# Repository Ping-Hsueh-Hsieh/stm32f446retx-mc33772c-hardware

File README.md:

# TODO

- [x] fill region: In1.Cu with GND
- [x] change 16MHz crystal to 8MHz, since 8MHz is cheaper and more available.
- [x] USB OTG FS: VBUS senisng
- [ ] stitching & fencing vias
- [x] shrink the board

# Sources

- [step-by-step tutorial](https://github.com/gt-marine-robotics-group/kicad-tutorial)
- [video](https://fedevel.com/blog/kicad-stm32-hardware-design-an-overview-in-20-minutes-phils-lab-15)
- [kicad footprints](https://gitlab.com/kicad/libraries/kicad-footprints)
- [reverse engineering KiCad Project from Gerber file](https://forum.kicad.info/t/reverse-engineering-kicad-project-from-gerber-files/30903)
- [STM32H742Vx 144 template](https://github.com/dmitrystu/nuco-v/blob/master/nuco-v.pdf)
- [STM32F446RETx sample](https://github.com/r4hulrr/stm-32-bms)

# ST-LINK

Test on NUCLEO-F446ZE with [configuration](./figs/how-to-connect-external-stlink-to-nucleo-f446ze.png) from [post](https://community.st.com/stm32-mcus-products-25/debugging-stm32f446ze-nucleo-swd-with-external-st-link-v2-155755?utm_source=chatgpt.com).
```
CN4.2 --> SWCLK
CN4.4 --> SWDIO
CN6.3 --> GND
```
with these pins connected, external ST-LINK V2 can be connected, debugging, even SWD with ITM.

# USB OTG FS

[VBUS sensing](https://community.st.com/stm32-mcus-60/management-of-vbus-sensing-for-usb-device-design-93)

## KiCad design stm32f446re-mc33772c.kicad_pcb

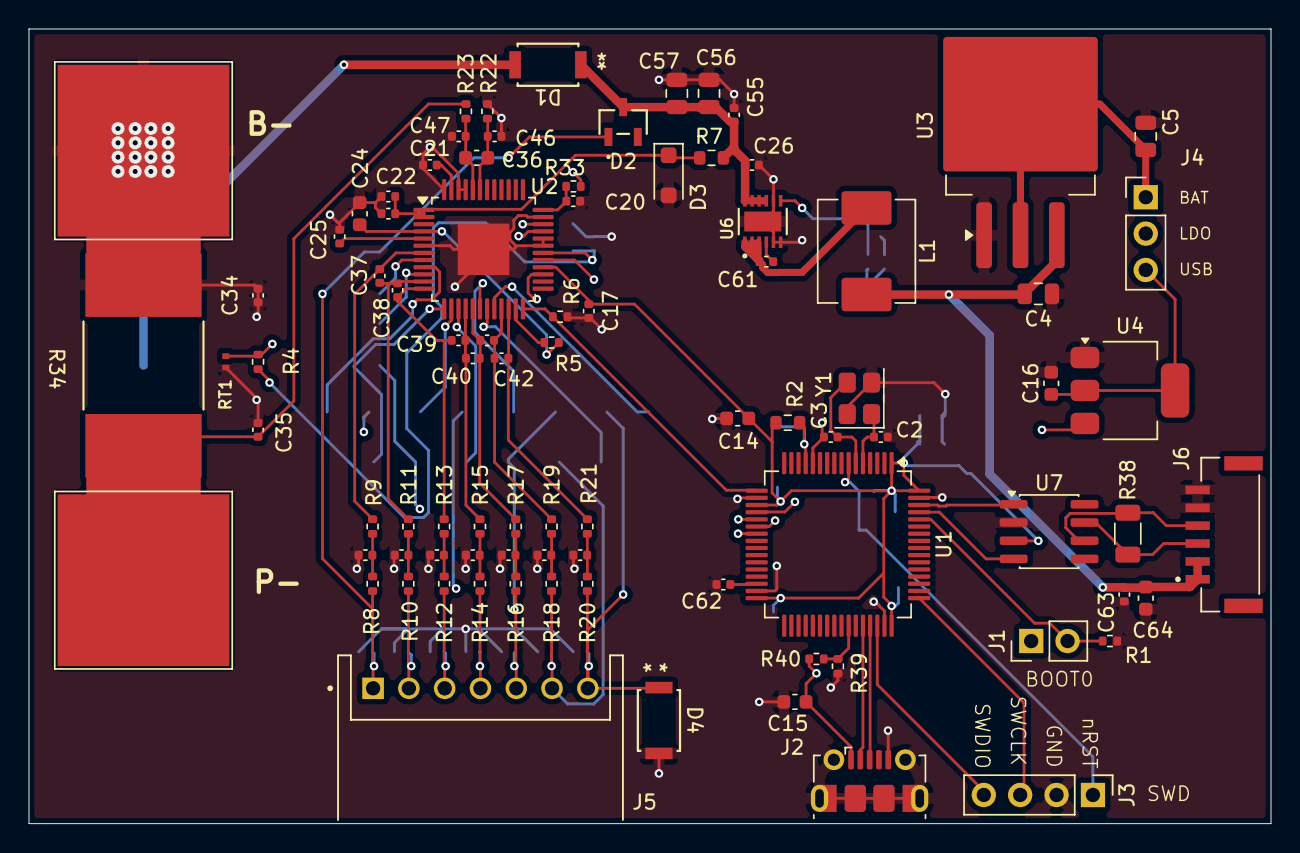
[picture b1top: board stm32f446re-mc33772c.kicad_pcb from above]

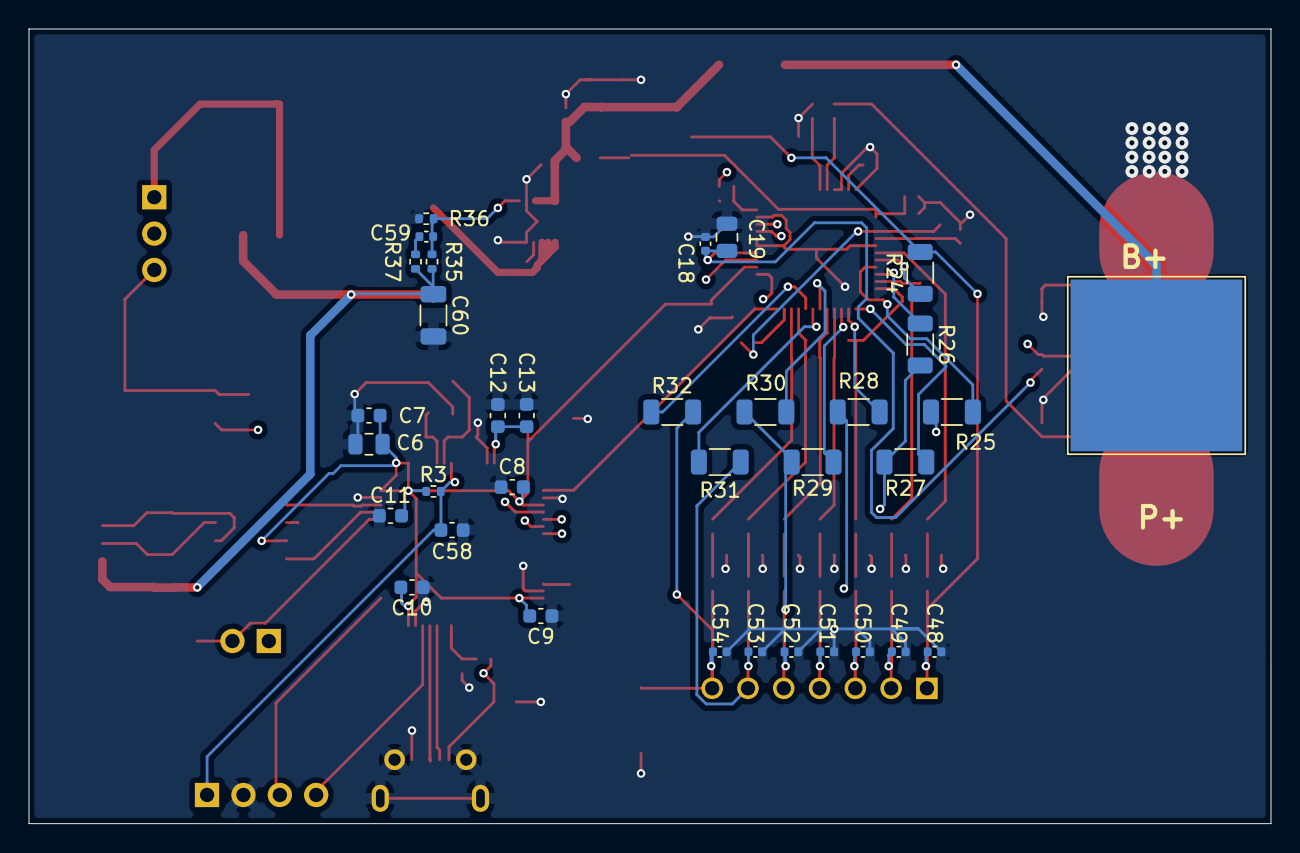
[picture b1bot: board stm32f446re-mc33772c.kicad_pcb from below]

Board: 4 copper layers, 86.8 x 55.5 mm, 122 parts (34 on the bottom side), 73 nets.

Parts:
C2, C3: 12p; C_0402_1005Metric
C4, C5, C6: 10u; C_0805_2012Metric
C7, C8, C9, C10, C11, C58: 100n; C_0603_1608Metric
C12: 10n; C_0603_1608Metric
C13, C14, C64: 1u; C_0603_1608Metric
C15, C16: 22u; C_0603_1608Metric
C17, C18, C27, C28, C29, C30, C31, C32, C33, C55, C61, C63: 100n; C_0402_1005Metric
C19: 2.2u; C_0805_2012Metric
C20: 1200p; C_0402_1005Metric
C21, C26, C34, C35, C46, C47, C48, C49, C50, C51, C52, C53, C54: 0.047u; C_0402_1005Metric
C22: 0.22u; C_0402_1005Metric
C23: 1000p; C_0402_1005Metric
C24: 0.47u; C_0603_1608Metric
C25, C37, C38, C39, C40, C41, C42: 0.01u; C_0402_1005Metric
C36: 6.8u; C_0603_1608Metric
C56, C57: 4.7u; C_0805_2012Metric
C59: 22p; C_0402_1005Metric
C60: 33u; C_1206_3216Metric
C62: 4.7u; C_0402_1005Metric
D1, D4: PMEG3050EP_115
D2: BAS40LT1G; BAS40LT1
D3: BZT52-C39_R1_00001; D_SOD-123F
J1: Conn_01x02; PinHeader_1x02_P2.54mm_Vertical
J2: USB_B_Micro; USB_Micro-B_Molex-105017-0001
J3: Conn_01x04; PinHeader_1x04_P2.54mm_Vertical
J4: Conn_01x03; PinHeader_1x03_P2.54mm_Vertical
J5: S7B-XH-A; JST_S7B-XH-A
J6: SM06B-GHS-TB; JST_SM06B-GHS-TB
L1: 3.3uH; PSPMAA0605H-3R3M-ANP
PAD1, PAD3, PAD4: pad; INPUT_PAD
R1, R3, R39: 10k; R_0402_1005Metric
R2: 120R; R_0603_1608Metric
R4, R5, R6: 10K; R_0402_1005Metric
R7: 6.8; R_0603_1608Metric
R8, R10, R12, R14, R16, R18, R20: 3.0K; R_0402_1005Metric
R9, R11, R13, R15, R17, R19, R21: 2.0K; R_0402_1005Metric
R22, R23: 127; R_0402_1005Metric
R24, R26, R27, R29, R30, R32: 68; R_1206_3216Metric
R25, R28, R31: 16; R_1206_3216Metric
R33: 3.3K; R_0402_1005Metric
R34: WSLP5931L1000FEA
R35: 100k; R_0402_1005Metric
R36: 19.1k; R_0402_1005Metric
R37: 1k; R_0402_1005Metric
R38: 120; R_1206_3216Metric
R40: 4.7k; R_0402_1005Metric
RT1: NTCG104BH103HT1; THERM_NTCG104BH103HT1
U1: STM32F446RET6; LQFP-64_10x10mm_P0.5mm
U2: MC33772CTP1AE; LQFP-48-1EP_7x7mm_P0.5mm_EP3.6x3.6mm
U3: LD1086D2M33TR; TO-263-3_TabPin2
U4: AMS1117-3.3; SOT-223-3_TabPin2
U6: LMR51450SDRRR
U7: SN65HVD232; SOIC-8_3.9x4.9mm_P1.27mm
Y1: 8MHz; Crystal_SMD_3225-4Pin_3.2x2.5mm

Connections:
AFE_CB_1: R32.1, U2.20 (CB_1)
AFE_CB_2: R30.1, U2.18 (CB_2)
AFE_CB_2:1_C: R31.1, U2.19 (CB_2:1_C)
AFE_CB_3: R29.1, U2.15 (CB_3)
AFE_CB_4: R27.1, U2.13 (CB_4)
AFE_CB_4:3_C: R28.1, U2.14 (CB_4:3_C)
AFE_CB_5: R26.1, U2.10 (CB_5)
AFE_CB_6: R24.1, U2.8 (CB_6)
AFE_CB_6:5_C: R25.1, U2.9 (CB_6:5_C)
AFE_CT_1: C41.2, C42.1, R19.1, U2.21 (CT_1)
AFE_CT_2: C40.2, C41.1, R17.1, U2.17 (CT_2)
AFE_CT_3: C39.2, C40.1, R15.1, U2.16 (CT_3)
AFE_CT_4: C38.2, C39.1, R13.1, U2.12 (CT_4)
AFE_CT_5: C37.2, C38.1, R11.1, U2.11 (CT_5)
AFE_CT_6: C37.1, R9.1, U2.7 (CT_6)
AFE_CT_REF: C42.2, R21.1, U2.22 (CT_REF)
AFE_ISENSE+: C36.1, C46.2, R22.1, U2.43 (ISENSE+)
AFE_ISENSE-: C36.2, C47.2, R23.1, U2.44 (ISENSE-)
AFE_VCOM: C18.2, C19.2, R4.1, U2.30 (VCOM)
AFE_VPRE: C24.1, R5.2, U2.4 (VPRE)
AFE_VPWR: C22.1, C23.1, D3.1 (K), R7.2, U2.1 (VPWR2), U2.2 (VPWR1)
BAT_3.3V: C5.1, J4.1, U3.2 (OUT)
BP-C1M: C54.1, D4.1, J5.7, R20.2, R32.2
BP-C1P: C53.1, J5.6, R18.2, R31.2
BP-C2P: C52.1, J5.5, R16.2, R29.2, R30.2
BP-C3P: C51.1, J5.4, R14.2, R28.2
BP-C4P: C50.1, J5.3, R12.2, R26.2, R27.2
BP-C5P: C49.1, J5.2, R10.2, R25.2
BP-C6P: C48.1, D2.1 (A), J5.1, R8.2, R24.2
Buck_5V: C4.1, C60.1, C63.1, C64.1, J6.1, J6.2, L1.2, R35.1, R37.1, U3.3 (IN)
CANH: J6.3, R38.1, U7.7 (CANH)
CANL: J6.4, R38.2, U7.6 (CANL)
CAN_RX: U1.61 (CAN1_RX), U7.4 (R)
CAN_TX: U1.62 (CAN1_TX), U7.1 (D)
D+: J2.3 (D+), U1.45 (USB_OTG_FS_DP)
D-: J2.2 (D-), U1.44 (USB_OTG_FS_DM)
LDO_3.3V: C6.2, C7.2, C8.2, C9.2, C10.2, C11.2, C14.1, C17.2, J1.1, J4.2, R2.2, R3.1, U1.1 (VBAT), U1.19 (VDD), U1.32 (VDD), U1.48 (VDD), U1.64 (VDD), U2.28 (VDDIO), U7.3 (VCC)
MC33772C_RESET: R6.1, U1.17 (PA3), U2.24 (RESET)
NTC_0: C20.1, R33.1, U2.36 (AN0/GPIO0)
unnamed: C27.1, R8.1, R9.2
unnamed: C28.1, R10.1, R11.2
unnamed: C29.1, R12.1, R13.2
unnamed: C30.1, R14.1, R15.2
unnamed: C31.1, R16.1, R17.2
unnamed: C32.1, R18.1, R19.2
unnamed: C33.1, R20.1, R21.2
unnamed: C59.1, R37.2
unnamed: J1.2, R1.1, U1.60 (BOOT0)
unnamed: R4.2, R33.2, RT1.1
unnamed: R39.1, R40.2, U1.42 (USB_OTG_FS_VBUS)
unnamed: C2.1, U1.5 (PH0), Y1.1
unnamed: C3.1, U1.6 (PH1), Y1.3
unnamed: C62.1, U1.30 (VCAP_1)
unnamed: C12.1, C13.1, R2.1, U1.13 (VDDA)
unnamed: R5.1, U2.23 (SPI_COM_EN)
unnamed: C21.2, U2.47 (VANA)
unnamed: C61.1, U6.4 (BOOT)
unnamed: C59.2, R35.2, R36.1, U6.7 (FB)
unnamed: C61.2, L1.1, U6.1 (SW), U6.2 (SW__1), U6.3 (SW__2)
Pack-: C35.2, PAD4.1 (1_1), R23.2, R34.2
Pack_24V: D1.2, PAD1.1 (1_1)
Rsense_P: C2.2, C3.2, C4.2, C5.2, C6.1, C7.1, C8.1, C9.1, C10.1, C11.1, C12.2, C13.2, C14.2, C15.2, C16.2, C17.1, C18.1, C19.1, C20.2, C21.1, C22.2, C23.2, C24.2, C25.2, C26.2, C27.2, C28.2, C29.2, C30.2, C31.2, C32.2, C33.2, C34.1, C34.2, C35.1, C46.1, C47.1, C48.2, C49.2, C50.2, C51.2, C52.2, C53.2, C54.2, C55.2, C56.2, C57.2, C58.1, C60.2, C62.2, C63.2, C64.2, D3.2 (A), D4.2, J2.5 (GND), J2.SH (Shield), J3.2, J6.5, J6.6, PAD3.1 (1_1), R1.2, R6.2, R22.2, R34.1, R36.2, R39.2, RT1.2, U1.12 (VSSA), U1.18 (VSS), U1.31 (VSS), U1.47 (VSS), U1.63 (VSS), U2.6 (GNDCP), U2.31 (CGND), U2.32 (RDTX_OUT-), U2.35 (RDTX_OUT+), U2.45 (AGND), U2.46 (DGND), U2.48 (GNDSUB), U2.49 (GNDFLAG), U3.1 (ADJ/GND), U4.1 (GND), U6.5 (PG), U6.6 (RT), U6.8 (AGND), U6.13 (PGND), U7.2 (GND), Y1.2 (G), Y1.4 (G)
SPI1_MISO: U1.22 (SPI1_MISO), U2.27 (SO)
SPI1_MOSI: U1.23 (SPI1_MOSI), U2.34 (SI/RDTX_IN+)
SPI1_NSS: U1.20 (SPI1_NSS), U2.29 (CSB)
SPI1_SCK: U1.21 (SPI1_SCK), U2.33 (SCLK/RDTX_IN-)
SWCLK: J3.3, U1.49 (SYS_JTCK-SWCLK)
SWDIO: J3.4, U1.46 (SYS_JTMS-SWDIO)
USB_3.3V: C16.1, J4.3, U4.2 (VO)
VBAT_PROT_24V: C26.1, C55.1, C56.1, C57.1, D1.1, D2.3 (K), R7.1, U6.9 (EN), U6.10 (VIN), U6.11 (VIN__1), U6.12 (VIN__2)
VBUS_5V: C15.1, J2.1 (VBUS), R40.1, U4.3 (VI)
VCP: C25.1, U2.5 (VCP)
nRST: C58.2, J3.1, R3.2, U1.7 (NRST)
